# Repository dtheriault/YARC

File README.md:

# YARC Repository - Yavapai Amateur Radio Club

This repository is Public and contains files supporting talks given by NO1D at
various YARC meetings.

##Prototyping - Making PCB's in your Garage

First talk to YARC on how I make PCB's in my garage using the Toner Transfer
method.  Used ID Timer circuit as the example and handed out many to club
members.

##IDtimer -- Ham Identification Timer circuit 

Project was presented during an April 2016 talk on PCB Prototyping.  The ID
Circuit was used as an example of thru-hole and SMD PCB which was produced for
club members using the Toner Transfer method. ID Timer provides 2m, 3m, 5m,
10m or 15m timer functions.  Software written for ATtiny85 however can be used
on variety of other Arduino/AVR based chips with minor modifications.
Hardware files for the ID Circuit are Eagle v7.2 based and can be used to
print your own PCB's.

##Spotting -- Spotting/Skimming using SDR's

Talk was given at the June 2016 Hamfest at Embry Riddle University.  Presented
my experiences using RTLSDR and Hermes Lite SDR's as skimmers for CW, RTTY and
WSPR/JT9/JT65 modes.

##Repeater -- Talks on W7YRC Repeater

UHF Upgrade Project, Sept 2016 - Mt. Union 70cm machine

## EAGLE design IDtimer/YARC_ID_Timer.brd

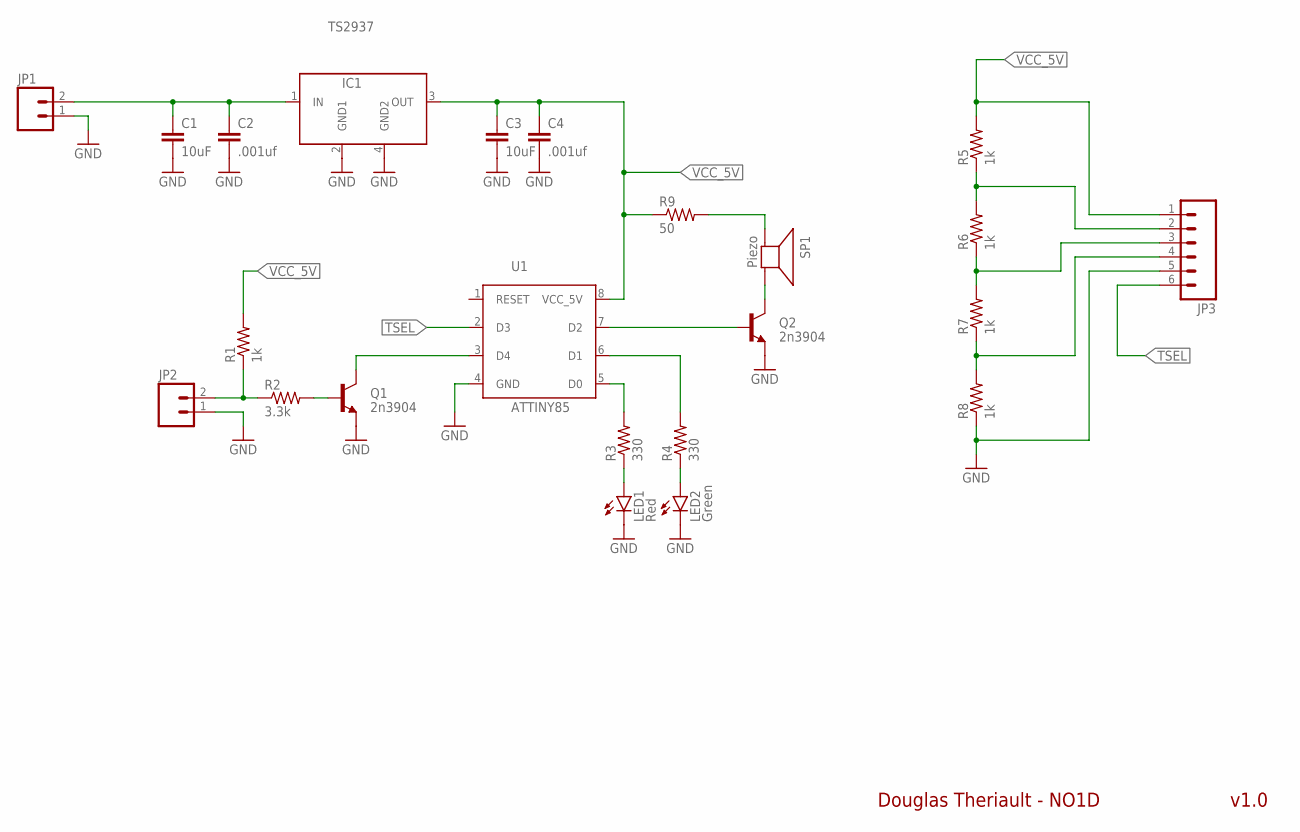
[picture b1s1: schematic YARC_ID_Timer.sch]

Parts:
C1: 10uF; 1210
C2, C4: .001uf; 0805
C3: 10uF; 0805
IC1: TS2937; SOT223
JP1, JP2: M02LOCK_LONGPADS; 1X02_LOCK_LONGPADS
JP3: M06LONGPADS; 1X06_LONGPADS
LED1: Red; LED5MM
LED2: Green; LED5MM
Q1, Q2: 2n3904; TO-92
R1, R5, R6, R7, R8: 1k; 0805
R2: 3.3k; 0805
R3, R4: 330; 0805
R9: 50; 0805
SP1: Piezo; AL60P
U1: ATTINY85; DIP08

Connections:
GND: C1.2, C2.2, C3.2, C4.2, IC1.2 (GND1), IC1.4 (GND2), JP1.1, JP2.1, JP3.5, LED1.K (C), LED2.K (C), Q1.1 (E), Q2.1 (E), R8.1, U1.4 (GND)
unnamed: LED1.A, R3.1
unnamed: Q2.2 (B), U1.7 (D2)
unnamed: Q2.3 (C), SP1.2 (-)
unnamed: R9.2, SP1.1 (+)
unnamed: LED2.A, R4.1
unnamed: R3.2, U1.5 (D0)
unnamed: R4.2, U1.6 (D1)
unnamed: Q1.3 (C), U1.3 (D4)
unnamed: Q1.2 (B), R2.2
unnamed: JP2.2, R1.1, R2.1
unnamed: C1.1, C2.1, IC1.1 (IN), JP1.2
unnamed: JP3.2, R5.1, R6.2
unnamed: JP3.3, R6.1, R7.2
unnamed: JP3.4, R7.1, R8.2
TSEL: JP3.6, U1.2 (D3)
VCC_5V: C3.1, C4.1, IC1.3 (OUT), JP3.1, R1.2, R5.2, R9.1, U1.8 (VCC_5V)

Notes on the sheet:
Douglas Theriault - NO1D
v1.0

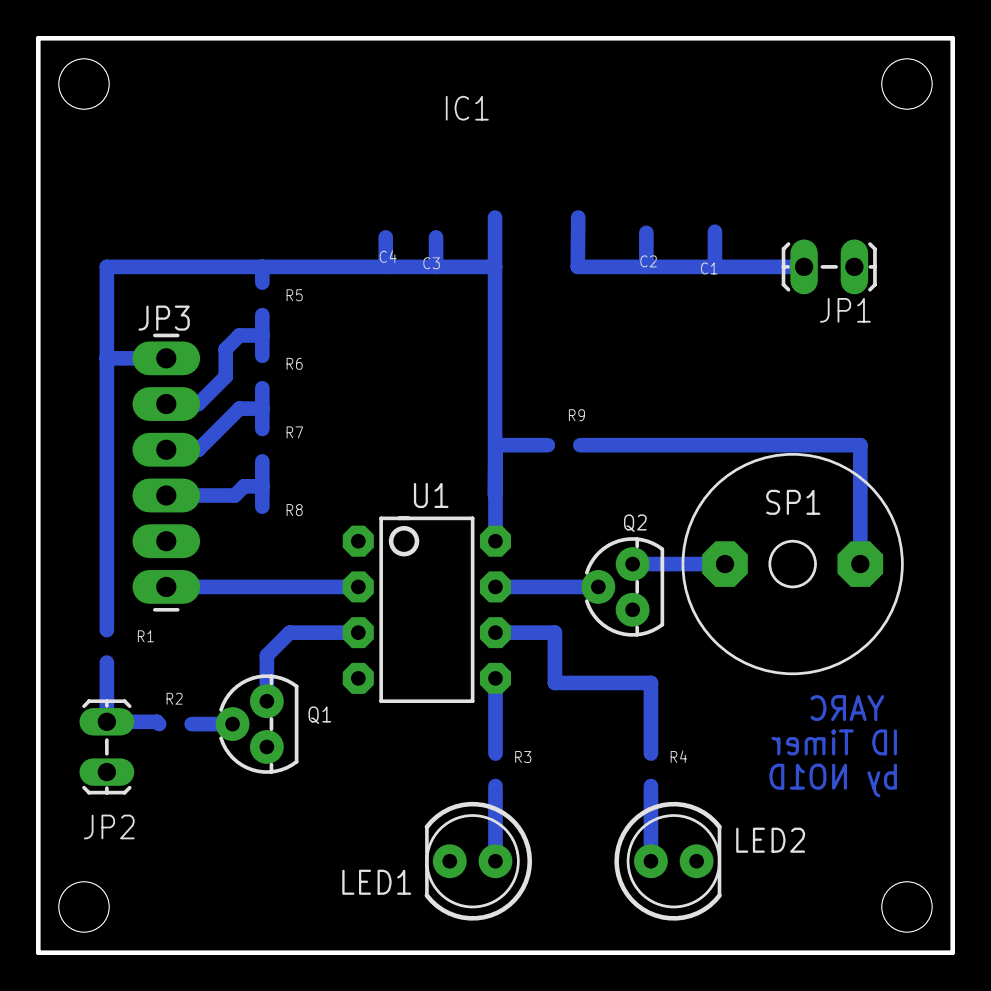
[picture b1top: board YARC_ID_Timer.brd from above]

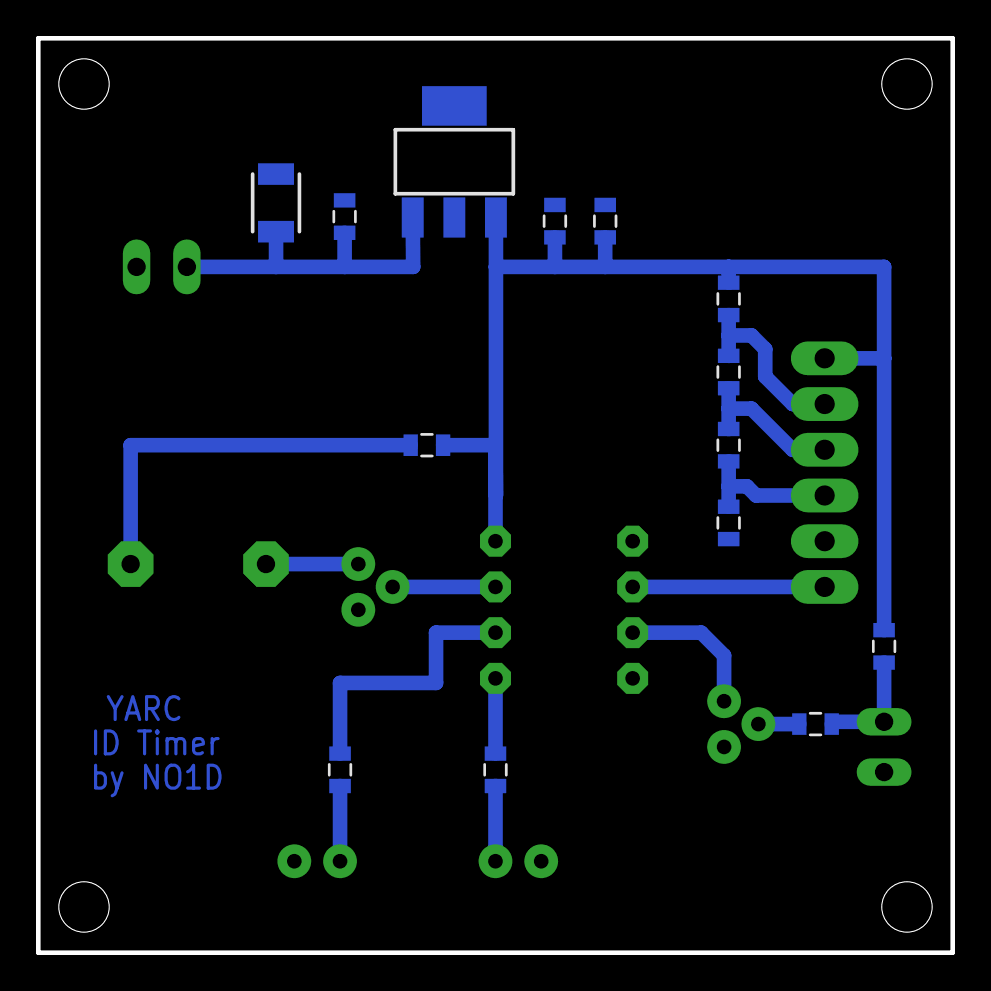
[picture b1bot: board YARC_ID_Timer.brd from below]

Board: 2 copper layers, 50.8 x 50.8 mm, 23 parts (14 on the bottom side), 17 nets.

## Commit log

2016-02-23 Initial submit for the ID timer project.
2016-02-23 Code cleanup, renamed directory so Arduino sketch tool works.
2016-02-23 New directory structure for Arduino sketch tool.
2016-02-23 Updated to reflect new repository structure.
2016-02-23 Headering
2016-04-04 Added support for setting OSCCAL register during setup. This value was tweaked for individual chips for the YARC IDT build. Use the Calibrate.ino sketch to recalibrate if necessary.
2016-04-04 Added Calibration routine to measure ATtiny85 internal clock on PB0 pin. You measure clock on this pin and tweak CALIBRATION define in order to get the RC clock to be pretty close (<1% of 4Mhz). Copy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
    Minor comments changes to IDTimer.ino
2016-04-04 Added Eagle schematic and board files along with PostScript files of Bottom Layer and Silk screen layer.
    Minor update to Readme.md
2016-04-04 Add files this time...
2016-04-05 Adding Specification in .odt and .pdf file formats
2016-04-05 Better schematic resolution for printing.
2016-04-05 One more try, darn schematic was printing poorly from .pdf and .odt.
2016-04-06 Adding Prototyping Directory
2016-04-07 Added CalibrationData.pdf which is the OSCCAL data measured for the 12 boards created for YARC. Folks who got boards and want to modify their ATtiny85 chip might want to adjust their OSCCAL define in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
2016-08-30 Spreadsheet source for IDTimer Calibration Data Added draft of MtUnion Upgrade Talk scheduled for Sept 2016 meeting.
2016-08-31 Final files for Sept 2016 club meeting talk on our UHF Repeater Upgrade effort. Source is the .odp file. .pdf, .ppt, .pptx output formats.
2016-08-31 Added files from June 2016 Hamfest Talk on Spotting using SDR.
2016-08-31 Upgrade Readme to reflect new directories and contents.
2016-09-06 Changed Tx PL tone to 131.8 per feedback from club meeting.
2017-07-03 Update to talks given over past 6 mos.

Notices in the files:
parts and their libraries:
SparkFun-Passives: Licensing: Creative Commons ShareAlike 4.0 International - https://creativecommons.org/licenses/by-sa/4.0
